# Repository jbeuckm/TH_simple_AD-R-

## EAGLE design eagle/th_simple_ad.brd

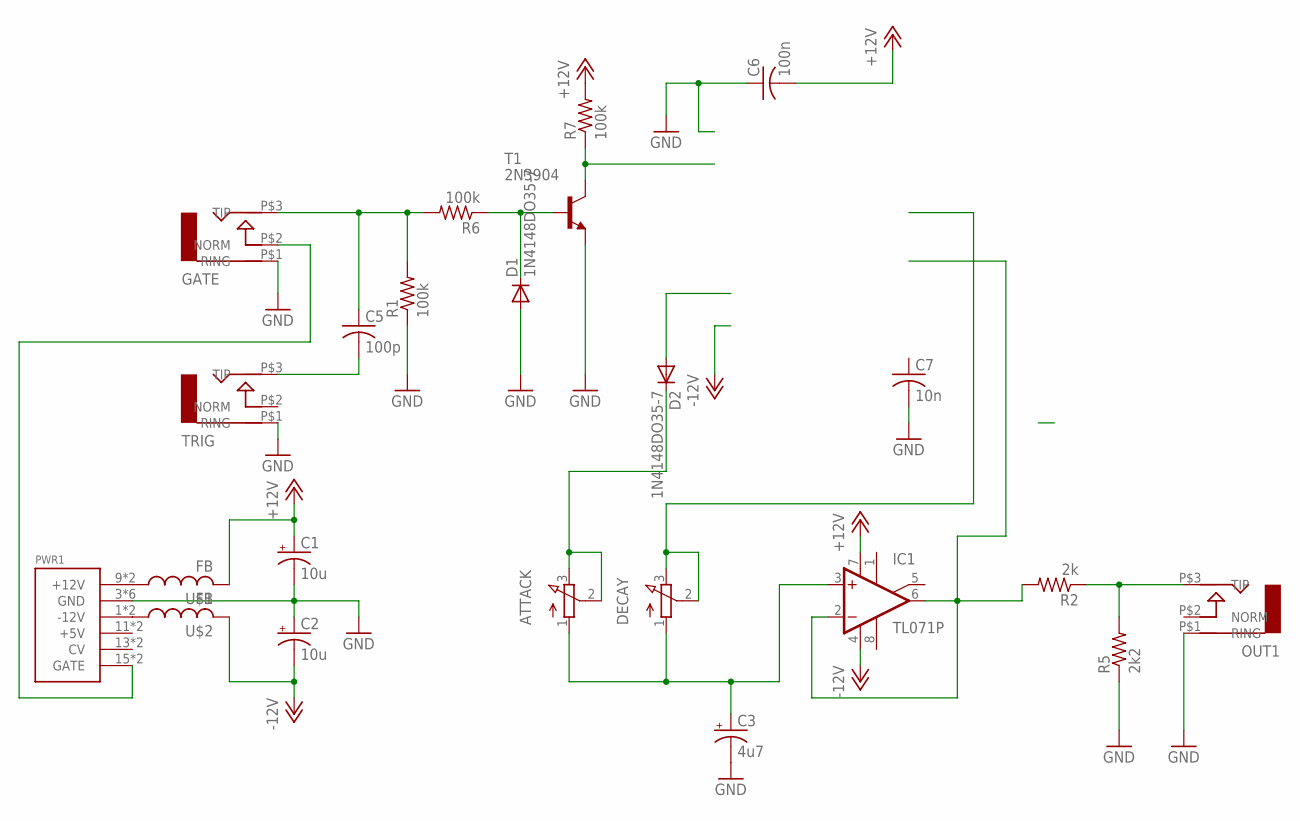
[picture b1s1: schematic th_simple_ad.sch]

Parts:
ATTACK: 3RP/1610N
C1, C2: 10u; B45181A
C3: 4u7; B45181A
C5: 100p; C050-024X044
C6: 100n; C050-024X044
C7: 10n; C050-024X044
D1, D2: 1N4148DO35-7; DO35-7
DECAY: 3RP/1610N
GATE: AUDIO-JACK; ERTHENVAR-JACK-90DEG
IC1: TL071P; DIL08
OUT1: AUDIO-JACK; ERTHENVAR-JACK-90DEG
PWR1: POWER; POWER_16
R1, R6, R7: 100k; 0207/10
R2: 2k; 0207/10
R5: 2k2; 0207/10
T1: 2N3904; TO92
TRIG: AUDIO-JACK; ERTHENVAR-JACK-90DEG
U$1, U$2: FB

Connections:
+12V: C1.+, C6.2, IC1.7 (V+), R7.2, U$1.P$2 (2); also elsewhere on the board
-12V: C2.-, IC1.4 (V-), U$2.P$2 (2)
GND: C1.-, C2.+, C3.-, C6.1, C7.2, D1.A, GATE.P$1 (RING), OUT1.P$1 (RING), PWR1.3 (GND), PWR1.4 (GND), PWR1.5 (GND), PWR1.6 (GND), PWR1.7 (GND), PWR1.8 (GND), R1.1, R5.1, T1.3 (E), TRIG.P$1 (RING); also elsewhere on the board
unnamed: PWR1.9 (+12V), PWR1.10 (+12V), U$1.P$1 (1)
unnamed: PWR1.1 (-12V), PWR1.2 (-12V), U$2.P$1 (1)
unnamed 5: OUT1.P$3 (TIP), R2.1, R5.2; also elsewhere on the board
unnamed 6: IC1.2 (-IN), IC1.6 (OUT), R2.2; also elsewhere on the board
unnamed: D1.C, R6.1, T1.2 (B)
unnamed 8: R7.1, T1.1 (C); also elsewhere on the board
unnamed 9: D2.A; also elsewhere on the board
unnamed: ATTACK.2 (S), ATTACK.3 (E), D2.C
unnamed 11: C7.1; also elsewhere on the board
unnamed 12: DECAY.2 (S), DECAY.3 (E); also elsewhere on the board
unnamed: GATE.P$2 (NORM), PWR1.15 (GATE), PWR1.16 (GATE)
unnamed: C5.2, TRIG.P$3 (TIP)
unnamed: C5.1, GATE.P$3 (TIP), R1.2, R6.2
unnamed: ATTACK.1 (A), C3.+, DECAY.1 (A), IC1.3 (+IN)

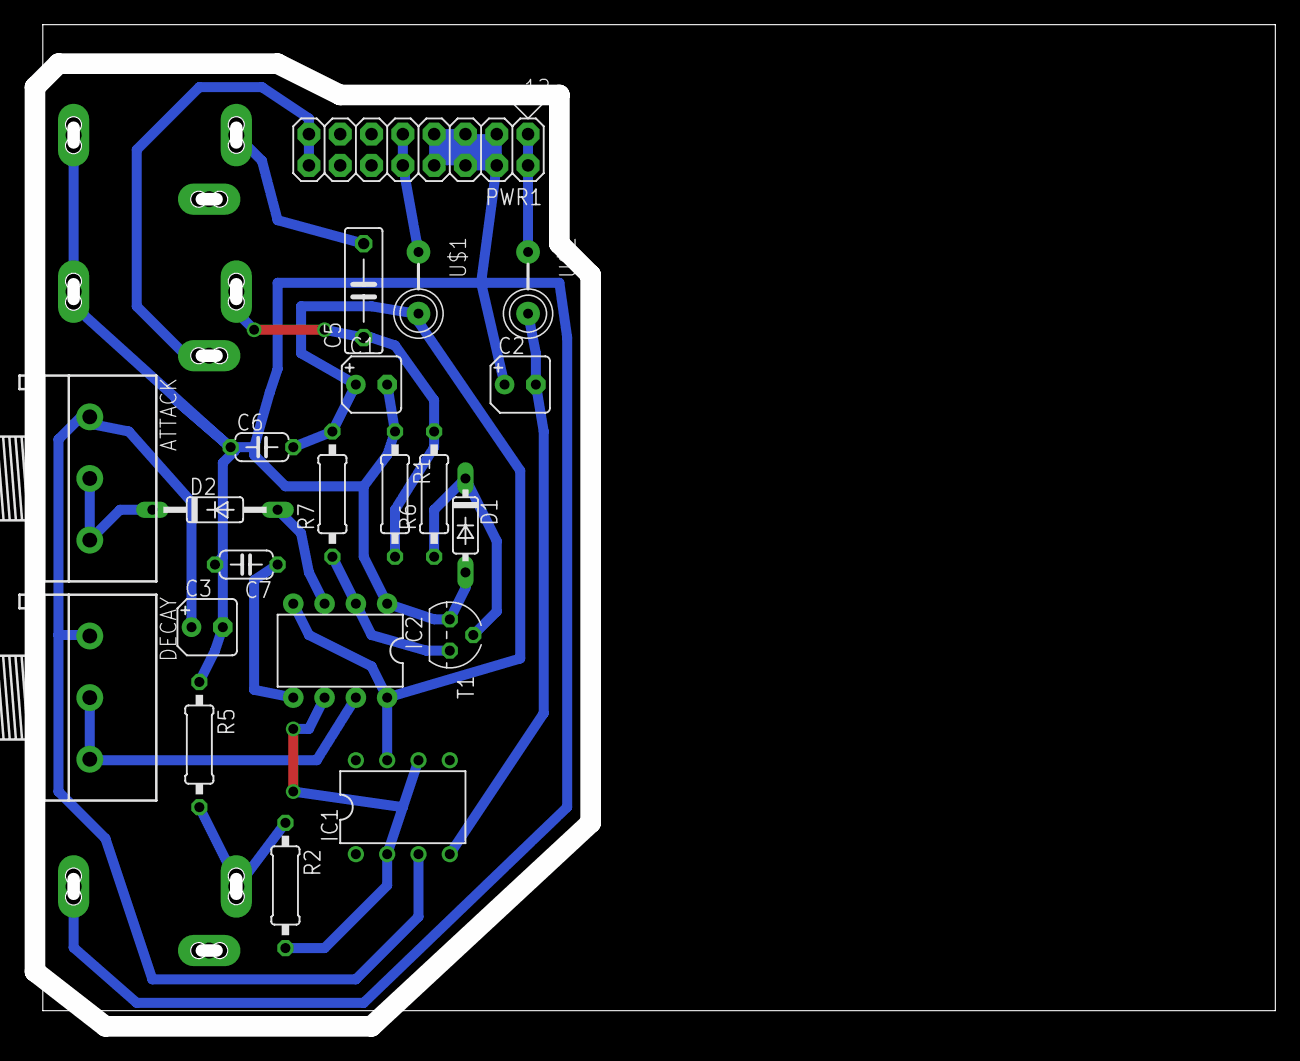
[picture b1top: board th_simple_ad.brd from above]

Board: 2 copper layers, 99.8 x 80.4 mm, 24 parts (0 on the bottom side), 17 nets.

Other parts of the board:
IC2: LM555N; DIL08-ROUND
OUT: AUDIO-JACK; ERTHENVAR-JACK-90DEG

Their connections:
+12V: IC2.4, IC2.8; also elsewhere on the board
GND: IC2.1, OUT.P$1; also elsewhere on the board
unnamed 5: OUT.P$3; also elsewhere on the board
unnamed 6: IC2.6; also elsewhere on the board
unnamed 8: IC2.2; also elsewhere on the board
unnamed 9: IC2.3; also elsewhere on the board
unnamed 11: IC2.5; also elsewhere on the board
unnamed 12: IC2.7; also elsewhere on the board

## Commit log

2015-12-31 schematic complete
2015-12-31 layout
2015-12-31 file structure and one fixed value
2015-12-31 vertical and cutout
2016-01-02 verified
